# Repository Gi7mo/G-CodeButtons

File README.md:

**G-Code Button PCB for [Agent Cain's Gcode Buttons](https://github.com/Agent-Cain/VoronUsers/tree/Voron-2_RGB_G-Code_Button/printer_mods/Agent-Cain/rgb_gcode-button)**

**BOM**
|Part NO.  |Qty  |LCSC  |Ali|
|--|--|--|--|
| Conn_01x03 | 1 | C131339 |[Link](https://s.click.aliexpress.com/e/_DlHystD)|
| Conn_01x04 | 1 | C131334 |[Link](https://s.click.aliexpress.com/e/_DlHystD)|
| WS2812-5050 | 1 | C114586 |[Link](https://s.click.aliexpress.com/e/_DCDujNX)|
| ROMER_G | 1 | --- |[Link](https://s.click.aliexpress.com/e/_DEeJCu3)|

**Assembly**
- Order the pcb at e.g. [pcbway](https://www.pcbway.com/project/shareproject/G_Code_Button_PCB_for_Agent_Cain_s_Gcode_Buttons_28c76498.html) or [jlcpcb](https://jlcpcb.com/)
- Order the buttons at e.g. [aliexpress](https://s.click.aliexpress.com/e/_DEeJCu3)
- Order the PH connectors at e.g. [aliexpress](https://s.click.aliexpress.com/e/_DdgpLUT)
- Assemble the PCB, the led is solderable by hand with a fine tip
- Wire up the pcbs to your controller
    - You can wire multiple pcb's in series, just go from data out (DO) to data in (DI) and expose only the switch (SW) cable for every pcb to your controller
- Add them as gcode buttons to your config
```
[gcode_button _EMERGENCY]
pin: ^!PE8
press_gcode:
    M112
```

- if you wan't e.g. a color change during press and macro execution, you can do it like this
```
[gcode_button _FILAMENT_UNLOAD]
pin: ^!PC12
press_gcode:
    SET_LED LED=buttons RED=1 GREEN=0 BLUE=0 index=2
    FILAMENT_UNLOAD
    SET_LED LED=buttons RED=1 GREEN=0.5 BLUE=0 index=2
```
- 
- 
- 

## Troubleshooting
- Problem: My Leds showing Random colors
    - Solution: Add a ~400Ω Resistor on the data line

## Notes
- You can contact me via Discord "Gi7mo!#4618"
- This readme file contains Amazon Associate, Aliexpress affiliate, PCBWay affiliate links. I make a comission on qualifying purchases.
- This project does not come with any warranty, if you choose to build/use one, you are doing this at your own risk!

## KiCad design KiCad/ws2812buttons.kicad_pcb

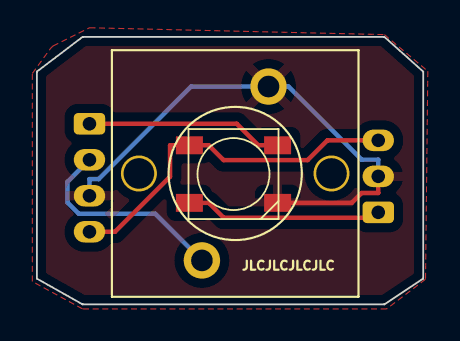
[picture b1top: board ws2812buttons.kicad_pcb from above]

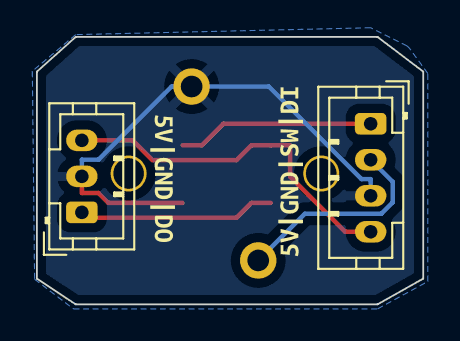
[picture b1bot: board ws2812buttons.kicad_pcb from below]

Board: 2 copper layers, 21.5 x 14.9 mm, 6 parts (4 on the bottom side), 5 nets.

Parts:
D1: WS2812B; LED_WS2812B_PLCC4_5.0x5.0mm_P3.2mm
J1: Conn_01x04_Male; JST_PH_B4B-PH-K_1x04_P2.00mm_Vertical
J2: Conn_01x03_Male; JST_PH_B3B-PH-K_1x03_P2.00mm_Vertical
U1: B3K-T13L; Omron B3K-T13L
kibuzzard-62A4DD9F: G***; kibuzzard-62A4DD9F
kibuzzard-62B786EE: G***; kibuzzard-62B786EE

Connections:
+5V: D1.1 (VDD), J1.4, J2.3
/DIN: D1.4 (DIN), J1.1
/DOUT: D1.2 (DOUT), J2.1
GND: D1.3 (VSS), J1.3, J2.2, U1.1
unnamed: J1.2, U1.2

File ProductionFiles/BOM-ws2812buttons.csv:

Comment,Designator,Footprint,LCSC
Conn_01x03_Male,J2,JST_PH_B3B-PH-K_1x03_P2.00mm_Vertical,
Conn_01x04_Male,J1,JST_PH_B4B-PH-K_1x04_P2.00mm_Vertical,
WS2812B,D1,LED_WS2812B_PLCC4_5.0x5.0mm_P3.2mm,
B3K-T13L,U1,Omron B3K-T13L,

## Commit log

2022-07-18 add files
2022-07-30 add ph connectors
2022-07-30 fix link
2022-08-23 add license file
2022-09-14 add skirt image, add links
2023-03-25 fixes wrong README.md fixes #1
